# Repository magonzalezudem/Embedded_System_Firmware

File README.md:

# Embedded_System_Firmware
This file contains the micropython scripts that ran on the microcontrollers of the thesis entitled: "Energy-Saving Environment-Aware Path Loss Model in LoRa Wide Area Networks for Urban Environments based on Data-driven Techniques."

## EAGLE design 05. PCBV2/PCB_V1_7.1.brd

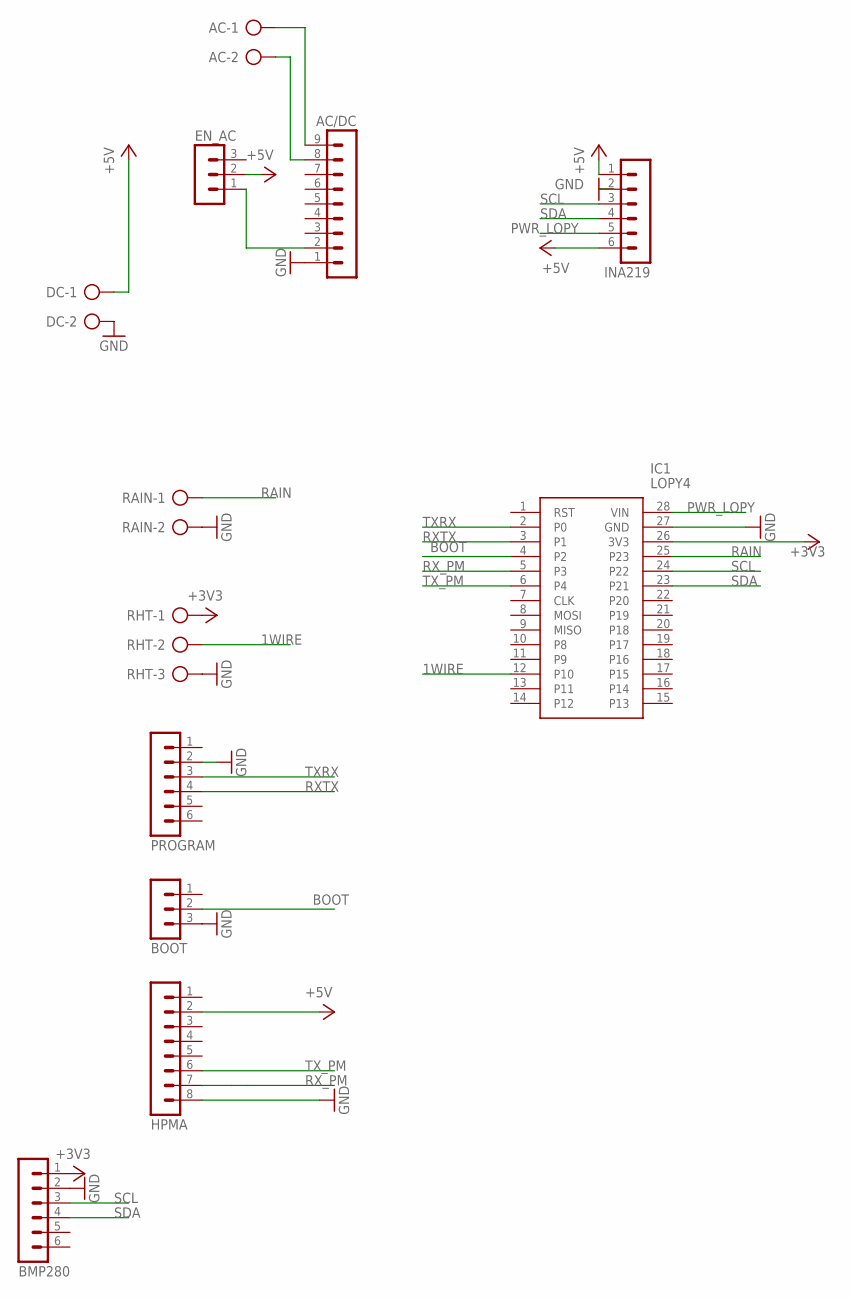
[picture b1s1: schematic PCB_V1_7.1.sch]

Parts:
AC: AK300/2
AC/DC: MA09-1
BMP280: MA06-1
BOOT: MA03-1
DC: AK300/2
EN_AC: MA03-1
HPMA: MA08-1
IC1: LOPY4
INA219: MA06-1
PROGRAM: MA06-1
RAIN: AK300/2
RHT: AK300/3

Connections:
1WIRE: IC1.12 (P10), RHT.2
+3V3: BMP280.1, IC1.26 (3V3), RHT.1
+5V: DC.1, EN_AC.2, HPMA.2, INA219.1, INA219.6
BOOT: BOOT.2, IC1.4 (P2)
GND: AC/DC.1, BMP280.2, BOOT.3, DC.2, HPMA.8, IC1.27 (GND), INA219.2, PROGRAM.2, RAIN.2, RHT.3
unnamed: AC.1, AC/DC.9
unnamed: AC.2, AC/DC.8
unnamed: AC/DC.2, EN_AC.1
PWR_LOPY: IC1.28 (VIN), INA219.5
RAIN: IC1.25 (P23), RAIN.1
RXTX: IC1.3 (P1), PROGRAM.4
RX_PM: HPMA.7, IC1.5 (P3)
SCL: BMP280.3, IC1.24 (P22), INA219.3
SDA: BMP280.4, IC1.23 (P21), INA219.4
TXRX: IC1.2 (P0), PROGRAM.3
TX_PM: HPMA.6, IC1.6 (P4)

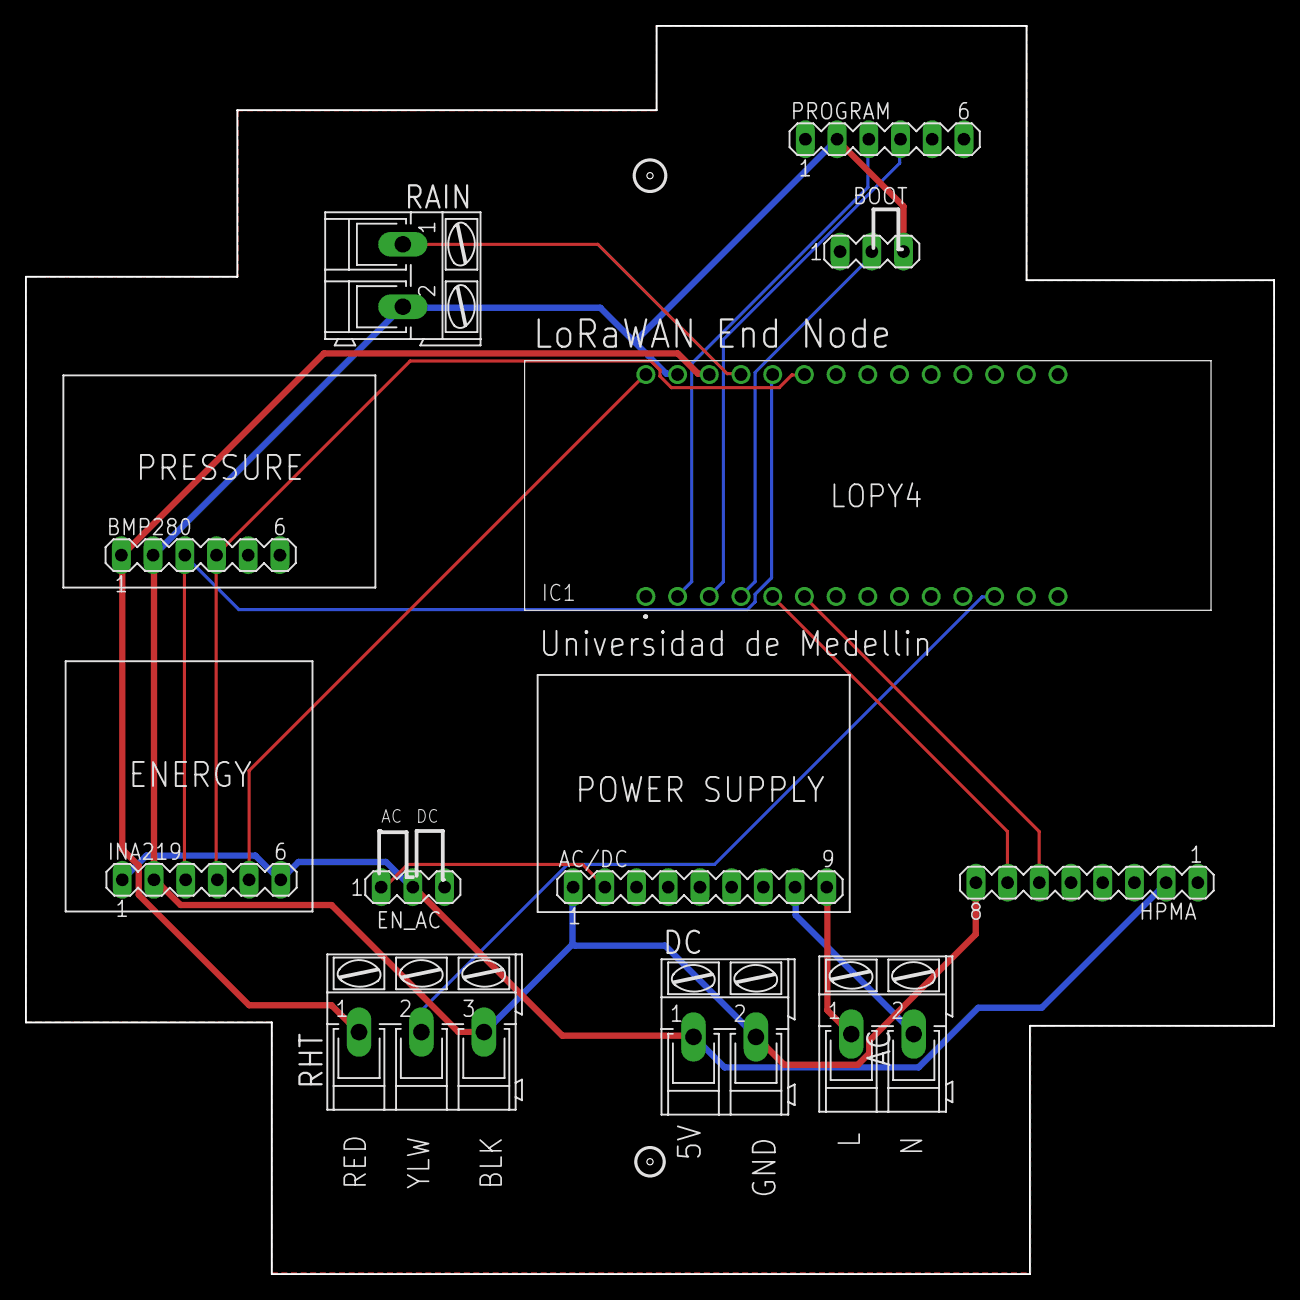
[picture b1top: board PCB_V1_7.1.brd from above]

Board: 2 copper layers, 100.0 x 100.0 mm, 12 parts (0 on the bottom side), 16 nets.
